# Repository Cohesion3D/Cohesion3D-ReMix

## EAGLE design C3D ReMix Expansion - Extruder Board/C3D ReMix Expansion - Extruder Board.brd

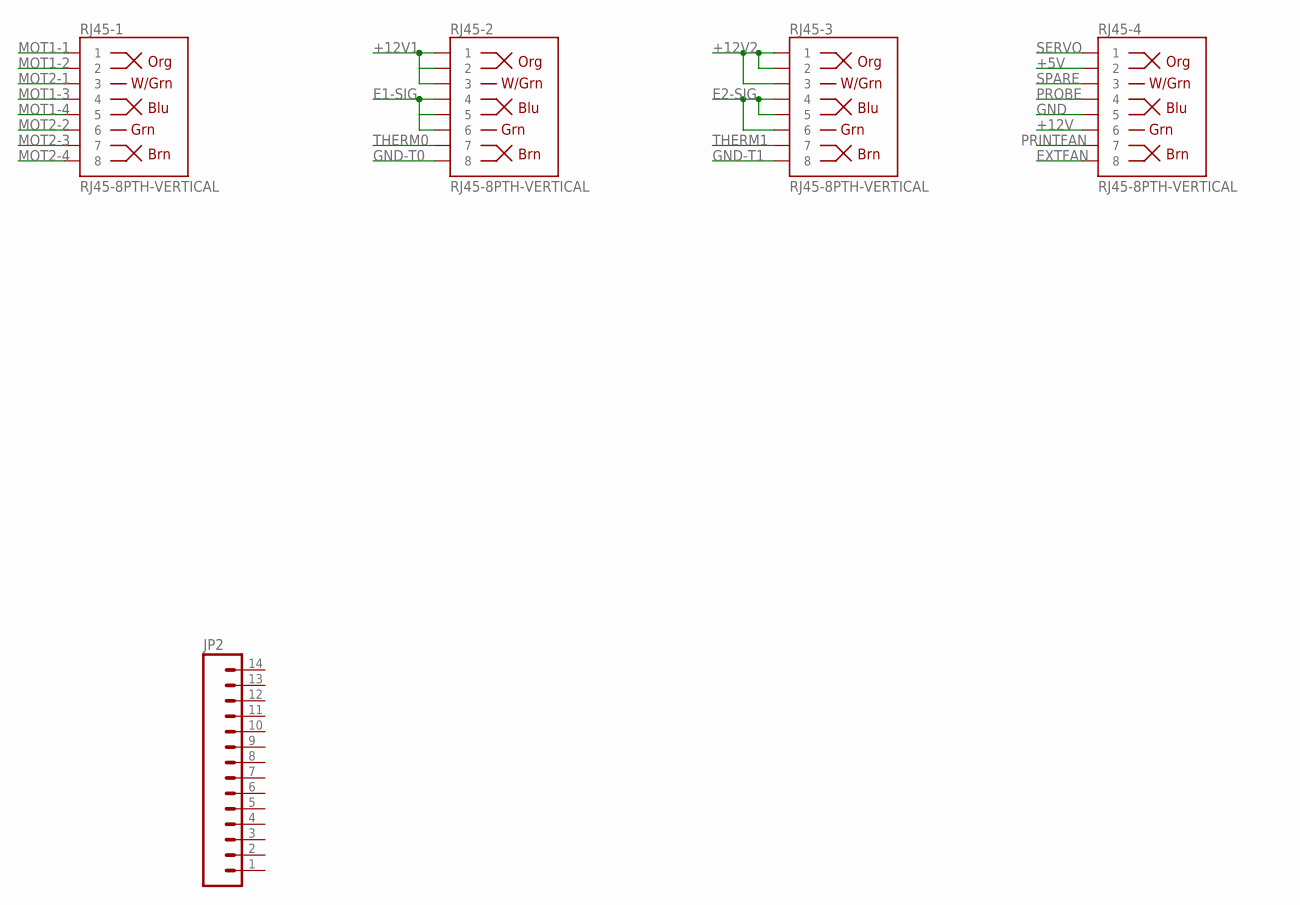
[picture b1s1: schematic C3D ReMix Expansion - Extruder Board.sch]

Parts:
JP2: M14; 1X14
RJ45-1, RJ45-2, RJ45-3, RJ45-4: RJ45-8PTH-VERTICAL; RJ45-8

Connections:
+5V: RJ45-4.2
+12V: RJ45-4.6
+12V1: RJ45-2.1, RJ45-2.2, RJ45-2.3
+12V2: RJ45-3.1, RJ45-3.2, RJ45-3.3
E1-SIG: RJ45-2.4, RJ45-2.5, RJ45-2.6
E2-SIG: RJ45-3.4, RJ45-3.5, RJ45-3.6
EXTFAN: RJ45-4.8
GND: RJ45-4.5
GND-T0: RJ45-2.8
GND-T1: RJ45-3.8
MOT1-1: RJ45-1.1
MOT1-2: RJ45-1.2
MOT1-3: RJ45-1.4
MOT1-4: RJ45-1.5
MOT2-1: RJ45-1.3
MOT2-2: RJ45-1.6
MOT2-3: RJ45-1.7
MOT2-4: RJ45-1.8
PRINTFAN: RJ45-4.7
PROBE: RJ45-4.4
SERVO: RJ45-4.1
SPARE: RJ45-4.3
THERM0: RJ45-2.7
THERM1: RJ45-3.7

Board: 2 copper layers, 5 parts (0 on the bottom side), 4 nets, no tracks yet.

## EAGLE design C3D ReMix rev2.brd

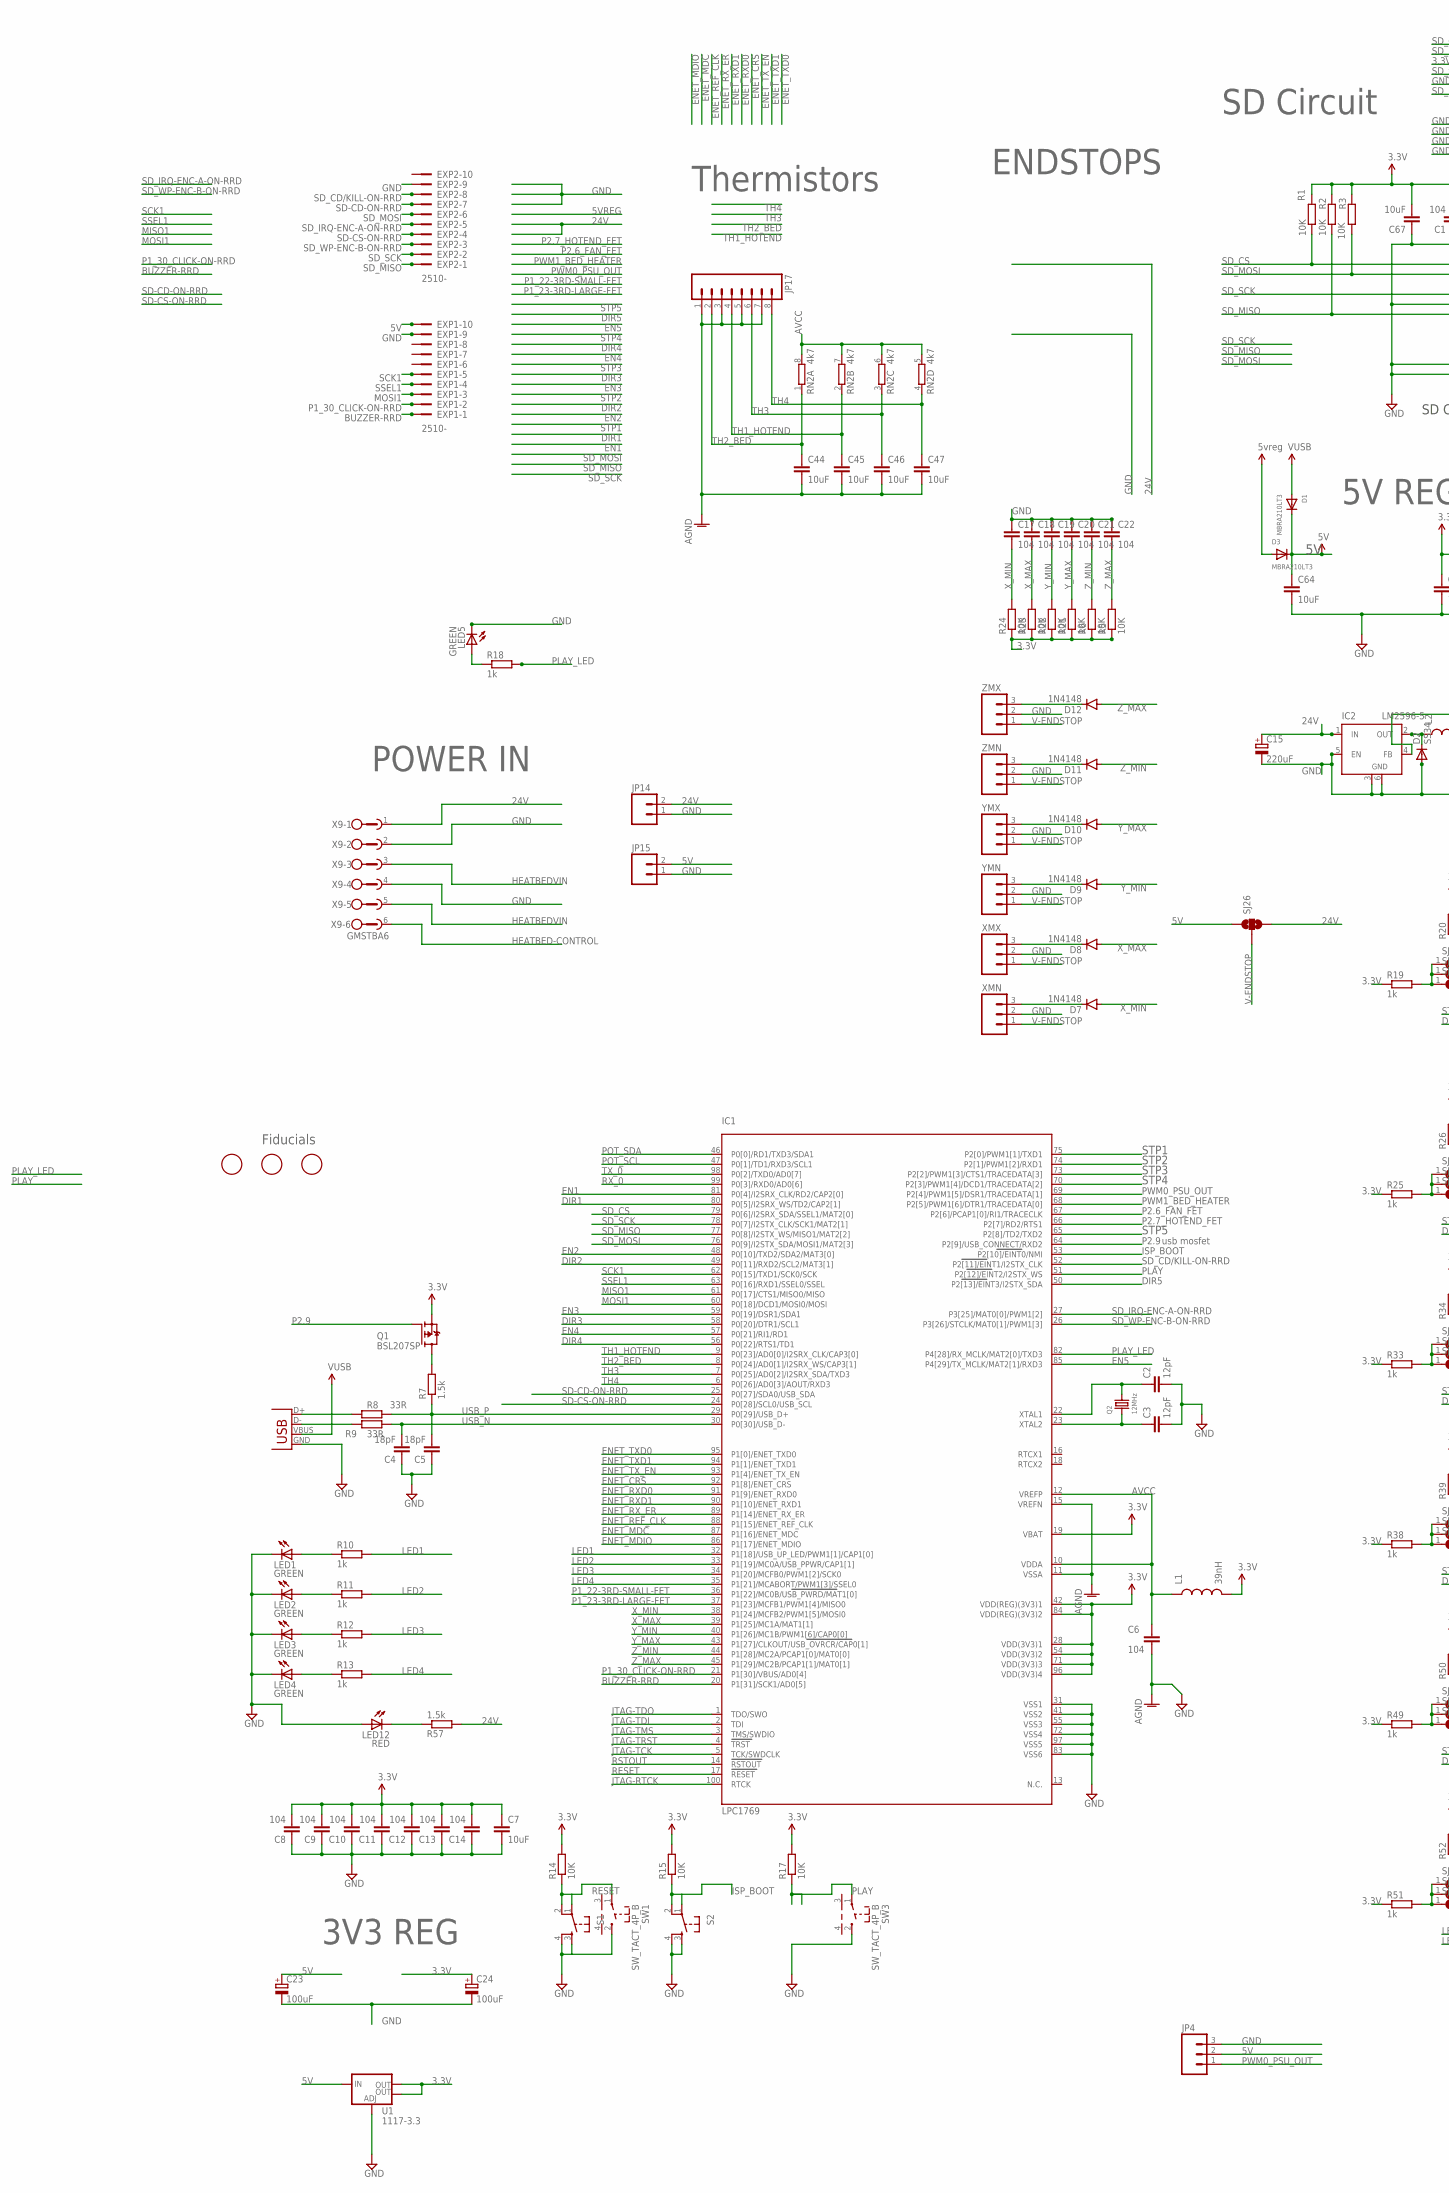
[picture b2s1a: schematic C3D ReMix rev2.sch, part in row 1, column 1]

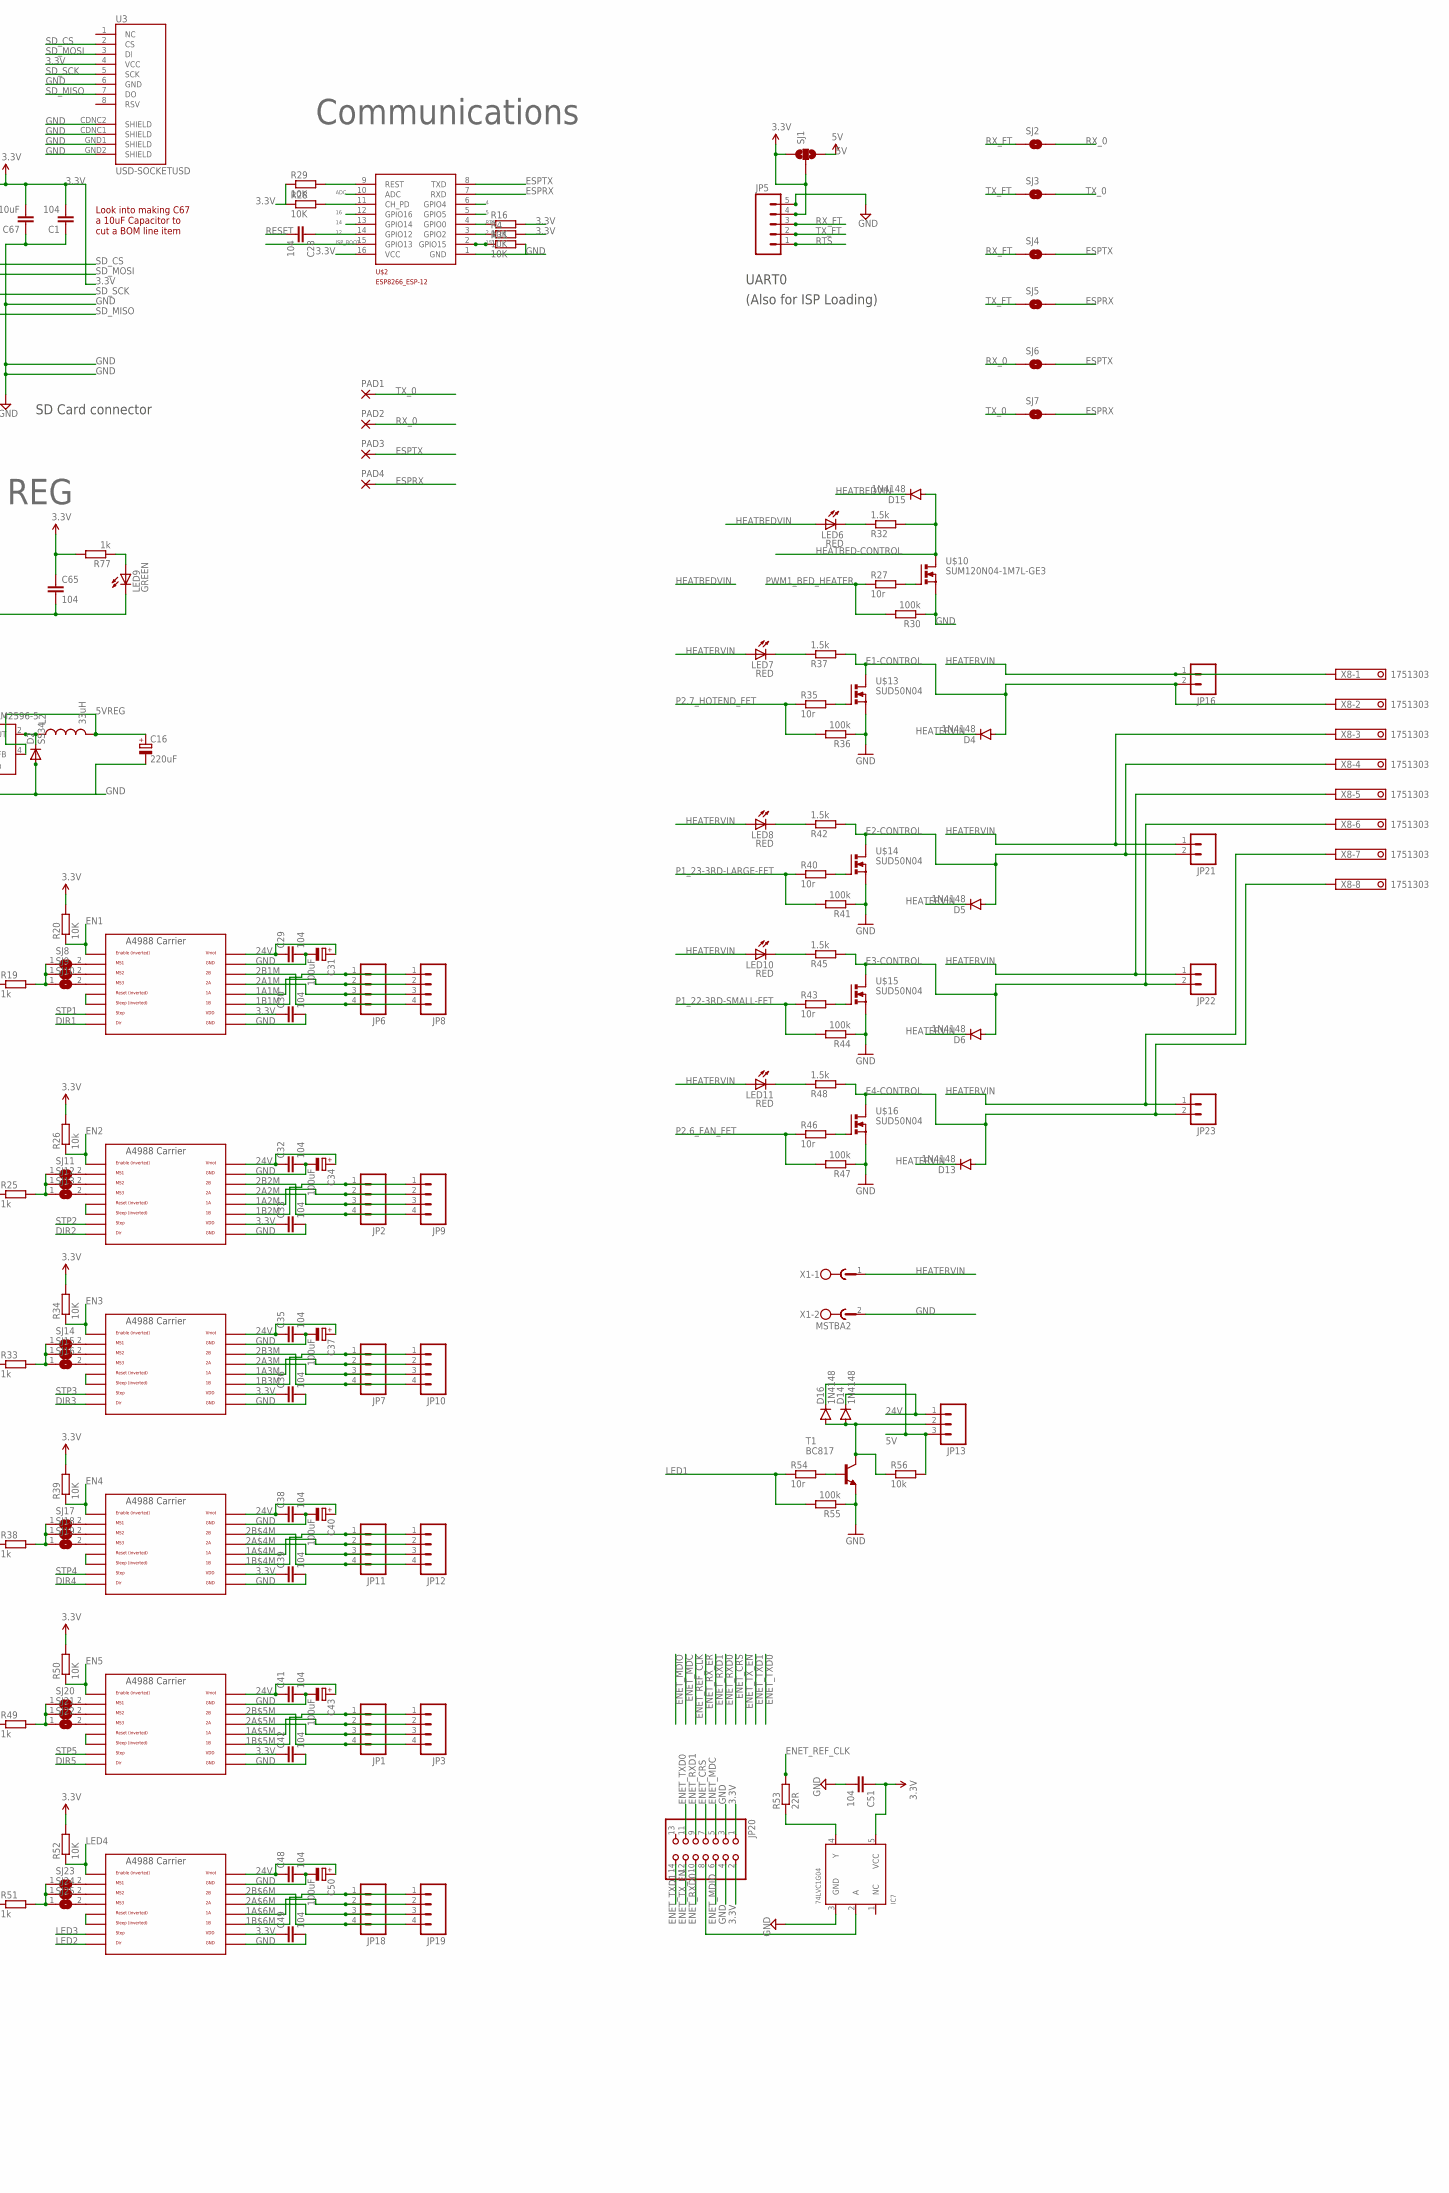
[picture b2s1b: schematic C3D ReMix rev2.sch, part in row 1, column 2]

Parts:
C1, C6, C8, C9, C10, C11, C12, C13, C14, C17, C18, C19, C20, C21, C22, C28, C29, C30, C32, C33, C35, C36, C38, C39, C41, C42, C48, C49, C51, C65: 104; C0603
C2, C3: 12pF; C0603
C4, C5: 18pF; C0603
C7, C44, C45, C46, C47, C64, C67: 10uF; C0603
C15, C16: 220uF; 153CLV-0810
C23, C24, C31, C34, C37, C40, C43, C50: 100uF; 153CLV-0605
D1, D3: MBRA210LT3; SMADIODE
D2: SS34; DO-214AC
D4, D5, D6, D7, D8, D9, D10, D11, D12, D13, D14, D15, D16: 1N4148; SOD-323
EXP1, EXP2: 2510-; PAK100/2500-10
IC1: LPC1769; LQFP100
IC2: LM2596-5; TO263-5
IC7: 74LVC1G04; SOT23-5
JP1, JP2, JP6, JP7, JP11, JP18: M04POLAR_LOCK; MOLEX-1X4_LOCK
JP3, JP8, JP9, JP10, JP12, JP19: M04LOCK; 1X04_LOCK
JP4, JP13: M03LOCK; 1X03_LOCK
JP5: M05NO_SILK; 1X05_NO_SILK
JP14, JP15, JP16, JP21, JP22, JP23: M02LOCK; 1X02_LOCK
JP17: M08LOCK; 1X08_LOCK
JP20: PINHD-2X7; 2X07
L1: 39nH; 0603
L2: 33uH; CDRH125
LED1, LED2, LED3, LED4, LED5, LED9: GREEN; SML0603
LED6, LED7, LED8, LED10, LED11, LED12: RED; SML0603
PAD1, PAD2, PAD3, PAD4: 1,6/0,9
Q1: BSL207SP; SC74_INFINEON
Q2: 12MHz; CRYSTAL_3.2X2.5
R1, R2, R3, R4, R5, R6, R14, R15, R16, R17, R20, R21, R22, R23, R24, R28, R29, R31, R34, R39, R50, R52: 10K; R0603
R7, R32, R37, R42, R45, R48, R57: 1.5k; R0603
R8, R9: 33R; R0603
R10, R11, R12, R13, R18, R19, R25, R33, R38, R49, R51, R77: 1k; R0603
R26, R56: 10k; R0603
R27, R35, R40, R43, R46, R54: 10r; R0603
R30, R36, R41, R44, R47, R55: 100k; R0603
R53: 22R; R0603
RN2: 4k7; 0603-ARV
S1, S2: TAC_SWITCHSMD; TACTILE_SWITCH_SMD
SJ1, SJ26: SOLDERJUMPER_2WAYS; SJ_3
SJ2, SJ3, SJ4, SJ5, SJ6, SJ7: SOLDERJUMPERNC; SJ_2S
SJ8, SJ9, SJ10, SJ11, SJ12, SJ13, SJ14, SJ15, SJ16, SJ17, SJ18, SJ19, SJ20, SJ21, SJ22, SJ23, SJ24, SJ25: SJ
SW1, SW3: SW_TACT_4P_B; SW_TACT_STANDARD_RIGHT_ANGLE
T1: BC817; SOT23-BEC
U1: 1117-3.3; SOT223
U3: USD-SOCKETUSD; USD-SOCKET-PP
U$1, U$5, U$6, U$7, U$8, U$9: POLOLU_A4983CARRIER; A4988BREAKOUT
U$2: ESP8266_ESP-12; ESP8266-ESP12
U$10: SUM120N04-1M7L-GE3; D2PACK
U$11, U$12, U$17: FIDUCIAL; FIDUCIAL_1MM
U$13, U$14, U$15, U$16: SUD50N04; D-PAK_TO252AA
X1: MSTBA2
X8: 1751303
X9: GMSTBA6
X14: USBPTH; USB-B-PTH
XMN: M03POLAR_LOCK; MOLEX-1X3_LOCK
XMX: M03POLAR_LOCK; MOLEX-1X3_LOCK
YMN: M03POLAR_LOCK; MOLEX-1X3_LOCK
YMX: M03POLAR_LOCK; MOLEX-1X3_LOCK
ZMN: M03POLAR_LOCK; MOLEX-1X3_LOCK
ZMX: M03POLAR_LOCK; MOLEX-1X3_LOCK

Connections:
1A1M: JP6.2, JP8.2, U$1.1A
1A2M: JP2.2, JP9.2, U$5.1A
1A3M: JP7.2, JP10.2, U$6.1A
1A$4M: JP11.2, JP12.2, U$7.1A
1A$5M: JP1.2, JP3.2, U$8.1A
1A$6M: JP18.2, JP19.2, U$9.1A
1B1M: JP6.1, JP8.1, U$1.1B
1B2M: JP2.1, JP9.1, U$5.1B
1B3M: JP7.1, JP10.1, U$6.1B
1B$4M: JP11.1, JP12.1, U$7.1B
1B$5M: JP1.1, JP3.1, U$8.1B
1B$6M: JP18.1, JP19.1, U$9.1B
2: R4.1, U$2.3 (GPIO2)
2A1M: JP6.3, JP8.3, U$1.2A
2A2M: JP2.3, JP9.3, U$5.2A
2A3M: JP7.3, JP10.3, U$6.2A
2A$4M: JP11.3, JP12.3, U$7.2A
2A$5M: JP1.3, JP3.3, U$8.2A
2A$6M: JP18.3, JP19.3, U$9.2A
2B1M: JP6.4, JP8.4, U$1.2B
2B2M: JP2.4, JP9.4, U$5.2B
2B3M: JP7.4, JP10.4, U$6.2B
2B$4M: JP11.4, JP12.4, U$7.2B
2B$5M: JP1.4, JP3.4, U$8.2B
2B$6M: JP18.4, JP19.4, U$9.2B
3.3V: C1.2, C7.1, C8.2, C9.2, C10.2, C11.2, C12.2, C13.2, C14.2, C24.+, C30.1, C33.1, C36.1, C39.1, C42.1, C49.1, C51.1, C65.1, C67.2, IC1.19 (VBAT), IC1.28 (VDD(3V3)1), IC1.42 (VDD(REG)(3V3)1), IC1.54 (VDD(3V3)2), IC1.71 (VDD(3V3)3), IC1.84 (VDD(REG)(3V3)2), IC1.96 (VDD(3V3)4), IC7.5 (VCC), JP5.4, JP20.1, JP20.2, L1.2, Q1.4 (S), R1.2, R2.2, R3.2, R4.2, R5.1, R6.1, R14.2, R15.2, R16.2, R17.2, R19.1, R20.2, R21.1, R22.1, R23.1, R24.1, R25.1, R26.2, R28.1, R29.1, R33.1, R34.2, R38.1, R39.2, R49.1, R50.2, R51.1, R52.2, R77.2, SJ1.1, SJ1.2, U1.2 (OUT), U1.4 (OUT), U3.4 (VCC), U$1.VDD, U$2.16 (VCC), U$5.VDD, U$6.VDD, U$7.VDD, U$8.VDD, U$9.VDD
4: U$2.6 (GPIO4)
5: U$2.5 (GPIO5)
5V: C23.+, C64.1, D1.C, D3.C, D16.C, EXP1.10, JP4.2, JP13.3, JP15.2, R56.2, SJ1.3, SJ26.1, U1.3 (IN)
5VREG: C16.+, D3.A, IC2.4 (FB), L2.2
12: C28.1, U$2.14 (GPIO12)
14: U$2.13 (GPIO14)
15: R31.1, U$2.2 (GPIO15)
16: U$2.12 (GPIO16)
24V: C15.+, C29.1, C31.+, C32.1, C34.+, C35.1, C37.+, C38.1, C40.+, C41.1, C43.+, C48.1, C50.+, D14.C, IC2.1 (IN), JP13.1, JP14.2, R57.2, SJ26.3, U$1.VMOT, U$5.VMOT, U$6.VMOT, U$7.VMOT, U$8.VMOT, U$9.VMOT, X9.1
ADC: U$2.10 (ADC)
AGND: C6.2, C44.2, C45.2, C46.2, C47.2, IC1.11 (VSSA), IC1.15 (VREFN), JP17.1, JP17.3, JP17.5, JP17.7
AVCC: C6.1, IC1.10 (VDDA), IC1.12 (VREFP), L1.1, RN2.5 (2), RN2.6 (2), RN2.7 (2), RN2.8 (2)
BUZZER-RRD: EXP1.1, IC1.20 (P1[31]/SCK1/AD0[5])
DIR1: IC1.80 (P0[5]/I2SRX_WS/TD2/CAP2[1]), U$1.DIR
DIR2: IC1.49 (P0[11]/RXD2/SCL2/MAT3[1]), U$5.DIR
DIR3: IC1.58 (P0[20]/DTR1/SCL1), U$6.DIR
DIR4: IC1.56 (P0[22]/RTS1/TD1), U$7.DIR
DIR5: IC1.50 (P2[13]/EINT3/I2STX_SDA), U$8.DIR
E1-CONTROL: D4.A, JP16.2, R37.2, U$13.4 (D), X8.2
E2-CONTROL: D5.A, JP21.2, R42.2, U$14.4 (D), X8.4
E3-CONTROL: D6.A, JP22.2, R45.2, U$15.4 (D), X8.6
E4-CONTROL: D13.A, JP23.2, R48.2, U$16.4 (D), X8.8
EN1: IC1.81 (P0[4]/I2SRX_CLK/RD2/CAP2[0]), R20.1, U$1.EN
EN2: IC1.48 (P0[10]/TXD2/SDA2/MAT3[0]), R26.1, U$5.EN
EN3: IC1.59 (P0[19]/DSR1/SDA1), R34.1, U$6.EN
EN4: IC1.57 (P0[21]/RI1/RD1), R39.1, U$7.EN
EN5: IC1.85 (P4[29]/TX_MCLK/MAT2[1]/RXD3), R50.1, U$8.EN
ENET_CRS: IC1.92 (P1[8]/ENET_CRS), JP20.7
ENET_MDC: IC1.87 (P1[16]/ENET_MDC), JP20.5
ENET_MDIO: IC1.86 (P1[17]/ENET_MDIO), JP20.6
ENET_REF_CLK: IC1.88 (P1[15]/ENET_REF_CLK), R53.2
ENET_RXD0: IC1.91 (P1[9]/ENET_RXD0), JP20.10
ENET_RXD1: IC1.90 (P1[10]/ENET_RXD1), JP20.9
ENET_RX_ER: IC1.89 (P1[14]/ENET_RX_ER)
ENET_TXD0: IC1.95 (P1[0]/ENET_TXD0), JP20.11
ENET_TXD1: IC1.94 (P1[1]/ENET_TXD1), JP20.14
ENET_TX_EN: IC1.93 (P1[4]/ENET_TX_EN), JP20.12
ESPRX: PAD4.1, SJ5.2, SJ7.2, U$2.7 (RXD)
ESPTX: PAD3.1, SJ4.2, SJ6.2, U$2.8 (TXD)
GND: C1.1, C2.2, C3.2, C4.1, C5.1, C7.2, C8.1, C9.1, C10.1, C11.1, C12.1, C13.1, C14.1, C15.-, C16.-, C17.1, C18.1, C19.1, C20.1, C21.1, C22.1, C23.-, C24.-, C29.2, C30.2, C31.-, C32.2, C33.2, C34.-, C35.2, C36.2, C37.-, C38.2, C39.2, C40.-, C41.2, C42.2, C43.-, C48.2, C49.2, C50.-, C51.2, C64.2, C65.2, C67.1, D2.2 (A), EXP1.9, EXP2.9, IC1.31 (VSS1), IC1.41 (VSS2), IC1.55 (VSS3), IC1.72 (VSS4), IC1.83 (VSS6), IC1.97 (VSS5), IC2.3 (GND), IC2.5 (EN), IC2.6 (GND), IC7.3 (GND), JP4.3, JP5.5, JP14.1, JP15.1, JP20.3, JP20.4, LED1.C, LED2.C, LED3.C, LED4.C, LED5.C, LED9.C, LED12.A, R30.1, R31.2, R36.1, R41.1, R44.1, R47.1, R55.1, S1.3, S1.4, S2.3, S2.4, SW1.2, SW3.2, T1.E, U1.1 (ADJ), U3.6 (GND), U3.CDNC1 (SHIELD), U3.CDNC2 (SHIELD), U3.GND1 (SHIELD), U3.GND2 (SHIELD), U$1.GND, U$1.GND@0 (GND), U$2.1 (GND), U$5.GND, U$5.GND@0 (GND), U$6.GND, U$6.GND@0 (GND), U$7.GND, U$7.GND@0 (GND), U$8.GND, U$8.GND@0 (GND), U$9.GND, U$9.GND@0 (GND), U$10.3 (S), U$13.3 (S), U$14.3 (S), U$15.3 (S), U$16.3 (S), X1.2, X9.2, X9.4, X14.GND, XMN.2, XMX.2, YMN.2, YMX.2, ZMN.2, ZMX.2
HEATBED-CONTROL: D15.A, R32.2, U$10.2 (D), X9.6
HEATBEDVIN: D15.C, LED6.A, X9.3, X9.5
HEATERVIN: D4.C, D5.C, D6.C, D13.C, JP16.1, JP21.1, JP22.1, JP23.1, LED7.A, LED8.A, LED10.A, LED11.A, X1.1, X8.1, X8.3, X8.5, X8.7
ISP_BOOT: IC1.53 (P2[10]/EINT0/NMI), R15.1, S2.1, S2.2, U$2.15 (GPIO13)
JTAG-RTCK: IC1.100 (RTCK)
JTAG-TCK: IC1.5 (TCK/SWDCLK)
JTAG-TDI: IC1.2 (TDI)
JTAG-TDO: IC1.1 (TDO/SWO)
JTAG-TMS: IC1.3 (TMS/SWDIO)
JTAG-TRST: IC1.4 (TRST)
LED1: IC1.32 (P1[18]/USB_UP_LED/PWM1[1]/CAP1[0]), R10.2, R54.1, R55.2
LED2: IC1.33 (P1[19]/MC0A/USB_PPWR/CAP1[1]), R11.2, U$9.DIR
LED3: IC1.34 (P1[20]/MCFB0/PWM1[2]/SCK0), R12.2, U$9.STEP
LED4: IC1.35 (P1[21]/MCABORT/PWM1[3]/SSEL0), R13.2, R52.1, U$9.EN
MISO1: IC1.61 (P0[17]/CTS1/MISO0/MISO)
MOSI1: EXP1.3, IC1.60 (P0[18]/DCD1/MOSI0/MOSI)
unnamed: C2.1, IC1.22 (XTAL1), Q2.2
unnamed: C3.1, IC1.23 (XTAL2), Q2.1
unnamed: LED5.A, R18.1
unnamed: D11.C, ZMN.3
unnamed: D10.C, YMX.3
unnamed: SJ8.2, U$1.MS1
unnamed: D9.C, YMN.3
unnamed: SJ9.2, U$1.MS2
unnamed: D2.1 (C), IC2.2 (OUT), L2.1
unnamed: SJ10.2, U$1.MS3
unnamed: D8.C, XMX.3
unnamed: U$5.RST, U$5.SLP (SLEEP)
unnamed: D7.C, XMN.3
unnamed: R25.2, SJ11.1, SJ12.1, SJ13.1
unnamed: SJ11.2, U$5.MS1
unnamed: D12.C, ZMX.3
unnamed: SJ12.2, U$5.MS2
unnamed: R28.2, U$2.11 (CH_PD)
unnamed: SJ13.2, U$5.MS3
unnamed: R27.2, U$10.1 (G)
unnamed: LED6.C, R32.1
unnamed: U$6.RST, U$6.SLP (SLEEP)
unnamed: LED12.C, R57.1
unnamed: R33.2, SJ14.1, SJ15.1, SJ16.1
unnamed: SJ14.2, U$6.MS1
unnamed: SJ15.2, U$6.MS2
unnamed: SJ16.2, U$6.MS3
unnamed: R35.2, U$13.1 (G)
unnamed: R19.2, SJ8.1, SJ9.1, SJ10.1
unnamed: LED7.C, R37.1
unnamed: U$7.RST, U$7.SLP (SLEEP)
unnamed: R38.2, SJ17.1, SJ18.1, SJ19.1
unnamed: SJ17.2, U$7.MS1
unnamed: SJ18.2, U$7.MS2
unnamed: U$1.RST, U$1.SLP (SLEEP)
unnamed: SJ19.2, U$7.MS3
unnamed: R40.2, U$14.1 (G)
unnamed: LED8.C, R42.1
unnamed: R43.2, U$15.1 (G)
unnamed: LED10.C, R45.1
unnamed: R46.2, U$16.1 (G)
unnamed: LED11.C, R48.1
unnamed: U$8.RST, U$8.SLP (SLEEP)
unnamed: R49.2, SJ20.1, SJ21.1, SJ22.1
unnamed: SJ20.2, U$8.MS1
unnamed: SJ21.2, U$8.MS2
unnamed: SJ22.2, U$8.MS3
unnamed: U$9.RST, U$9.SLP (SLEEP)
unnamed: R51.2, SJ23.1, SJ24.1, SJ25.1
unnamed: SJ23.2, U$9.MS1
unnamed: Q1.1 (D), Q1.2 (D), Q1.5 (D), Q1.6 (D), R7.2
unnamed: SJ24.2, U$9.MS2
unnamed: SJ25.2, U$9.MS3
unnamed: R54.2, T1.B
unnamed: D14.A, D16.A, JP13.2, R56.1, T1.C
unnamed: R8.1, X14.D+
unnamed: R9.1, X14.D-
unnamed: IC7.2 (A), JP20.8
unnamed: IC7.4 (Y), R53.1
unnamed: LED9.A, R77.1
unnamed: LED4.A, R13.1
unnamed: LED3.A, R12.1
unnamed: LED2.A, R11.1
unnamed: LED1.A, R10.1
P1_22-3RD-SMALL-FET: IC1.36 (P1[22]/MC0B/USB_PWRD/MAT1[0]), R43.1, R44.2
P1_23-3RD-LARGE-FET: IC1.37 (P1[23]/MCFB1/PWM1[4]/MISO0), R40.1, R41.2
P1_30_CLICK-ON-RRD: EXP1.2, IC1.21 (P1[30]/VBUS/AD0[4])
P2.6_FAN_FET: IC1.67 (P2[6]/PCAP1[0]/RI1/TRACECLK), R46.1, R47.2
P2.7_HOTEND_FET: IC1.66 (P2[7]/RD2/RTS1), R35.1, R36.2
P2.9: IC1.64 (P2[9]/USB_CONNECT/RXD2), Q1.3 (G)
PLAY: IC1.51 (P2[12]/EINT2/I2STX_WS), R17.1, SW3.1
PLAY_LED: IC1.82 (P4[28]/RX_MCLK/MAT2[0]/TXD3), R18.2
POT_SCL: IC1.47 (P0[1]/TD1/RXD3/SCL1)
POT_SDA: IC1.46 (P0[0]/RD1/TXD3/SDA1)
PWM0_PSU_OUT: IC1.69 (P2[4]/PWM1[5]/DSR1/TRACEDATA[1]), JP4.1
PWM1_BED_HEATER: IC1.68 (P2[5]/PWM1[6]/DTR1/TRACEDATA[0]), R27.1, R30.2
RESET: C28.2, IC1.17 (RESET), R14.1, S1.1, S1.2, SW1.1
RESET1: R29.2, U$2.9 (REST)
RSTOUT: IC1.14 (RSTOUT)
RTS: JP5.1, R16.1, U$2.4 (GPIO0)
RX_0: IC1.99 (P0[3]/RXD0/AD0[6]), PAD2.1, SJ2.2, SJ6.1
RX_FT: JP5.3, SJ2.1, SJ4.1
SCK1: EXP1.5, IC1.62 (P0[15]/TXD1/SCK0/SCK)
SD-CD-ON-RRD: EXP2.7, IC1.25 (P0[27]/SDA0/USB_SDA)
SD-CS-ON-RRD: EXP2.4, IC1.24 (P0[28]/SCL0/USB_SCL)
SD_CD/KILL-ON-RRD: EXP2.8, IC1.52 (P2[11]/EINT1/I2STX_CLK)
SD_CS: IC1.79 (P0[6]/I2SRX_SDA/SSEL1/MAT2[0]), R1.1, U3.2 (CS)
SD_IRQ-ENC-A-ON-RRD: EXP2.5, IC1.27 (P3[25]/MAT0[0]/PWM1[2])
SD_MISO: EXP2.1, IC1.77 (P0[8]/I2STX_WS/MISO1/MAT2[2]), R2.1, U3.7 (DO)
SD_MOSI: EXP2.6, IC1.76 (P0[9]/I2STX_SDA/MOSI1/MAT2[3]), R3.1, U3.3 (DI)
SD_SCK: EXP2.2, IC1.78 (P0[7]/I2STX_CLK/SCK1/MAT2[1]), U3.5 (SCK)
SD_WP-ENC-B-ON-RRD: EXP2.3, IC1.26 (P3[26]/STCLK/MAT0[1]/PWM1[3])
SSEL1: EXP1.4, IC1.63 (P0[16]/RXD1/SSEL0/SSEL)
STP1: IC1.75 (P2[0]/PWM1[1]/TXD1), U$1.STEP
STP2: IC1.74 (P2[1]/PWM1[2]/RXD1), U$5.STEP
STP3: IC1.73 (P2[2]/PWM1[3]/CTS1/TRACEDATA[3]), U$6.STEP
STP4: IC1.70 (P2[3]/PWM1[4]/DCD1/TRACEDATA[2]), U$7.STEP
STP5: IC1.65 (P2[8]/TD2/TXD2), U$8.STEP
TH1_HOTEND: C45.1, IC1.9 (P0[23]/AD0[0]/I2SRX_CLK/CAP3[0]), JP17.4, RN2.2 (1)
TH2_BED: C44.1, IC1.8 (P0[24]/AD0[1]/I2SRX_WS/CAP3[1]), JP17.2, RN2.1
TH3: C46.1, IC1.7 (P0[25]/AD0[2]/I2SRX_SDA/TXD3), JP17.6, RN2.3 (1)
TH4: C47.1, IC1.6 (P0[26]/AD0[3]/AOUT/RXD3), JP17.8, RN2.4 (1)
TX_0: IC1.98 (P0[2]/TXD0/AD0[7]), PAD1.1, SJ3.2, SJ7.1
TX_FT: JP5.2, SJ3.1, SJ5.1
USB_N: C4.2, IC1.30 (P0[30]/USB_D-), R9.2
USB_P: C5.2, IC1.29 (P0[29]/USB_D+), R7.1, R8.2
V-ENDSTOP: SJ26.2, XMN.1, XMX.1, YMN.1, YMX.1, ZMN.1, ZMX.1
VUSB: D1.A, X14.VBUS
X_MAX: C18.2, D8.A, IC1.39 (P1[25]/MC1A/MAT1[1]), R23.2
X_MIN: C17.2, D7.A, IC1.38 (P1[24]/MCFB2/PWM1[5]/MOSI0), R24.2
Y_MAX: C20.2, D10.A, IC1.43 (P1[27]/CLKOUT/USB_OVRCR/CAP0[1]), R21.2
Y_MIN: C19.2, D9.A, IC1.40 (P1[26]/MC1B/PWM1[6]/CAP0[0]), R22.2
Z_MAX: C22.2, D12.A, IC1.45 (P1[29]/MC2B/PCAP1[1]/MAT0[1]), R5.2
Z_MIN: C21.2, D11.A, IC1.44 (P1[28]/MC2A/PCAP1[0]/MAT0[0]), R6.2

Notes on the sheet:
SD Card connector
UART0
(Also for ISP Loading)
usb mosfet
5V REG
SD Circuit
Communications
3V3 REG
ENDSTOPS
Look into making C67 a 10uF Capacitor to cut a BOM line item
Thermistors
Fiducials
POWER IN

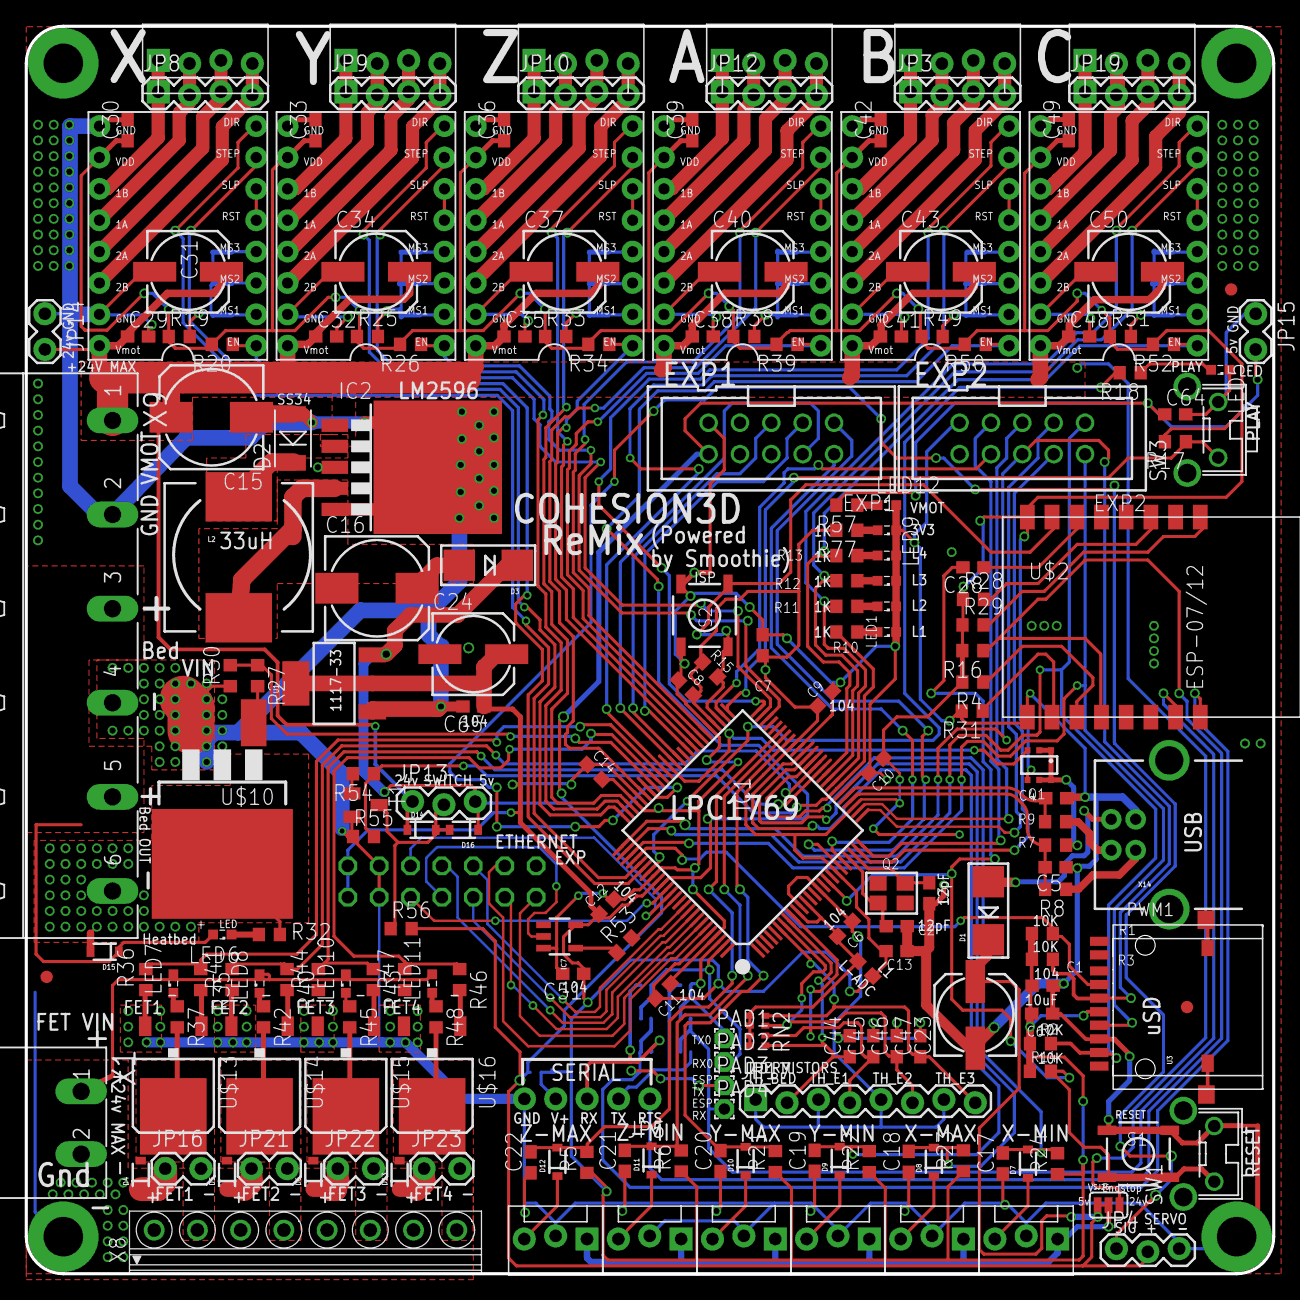
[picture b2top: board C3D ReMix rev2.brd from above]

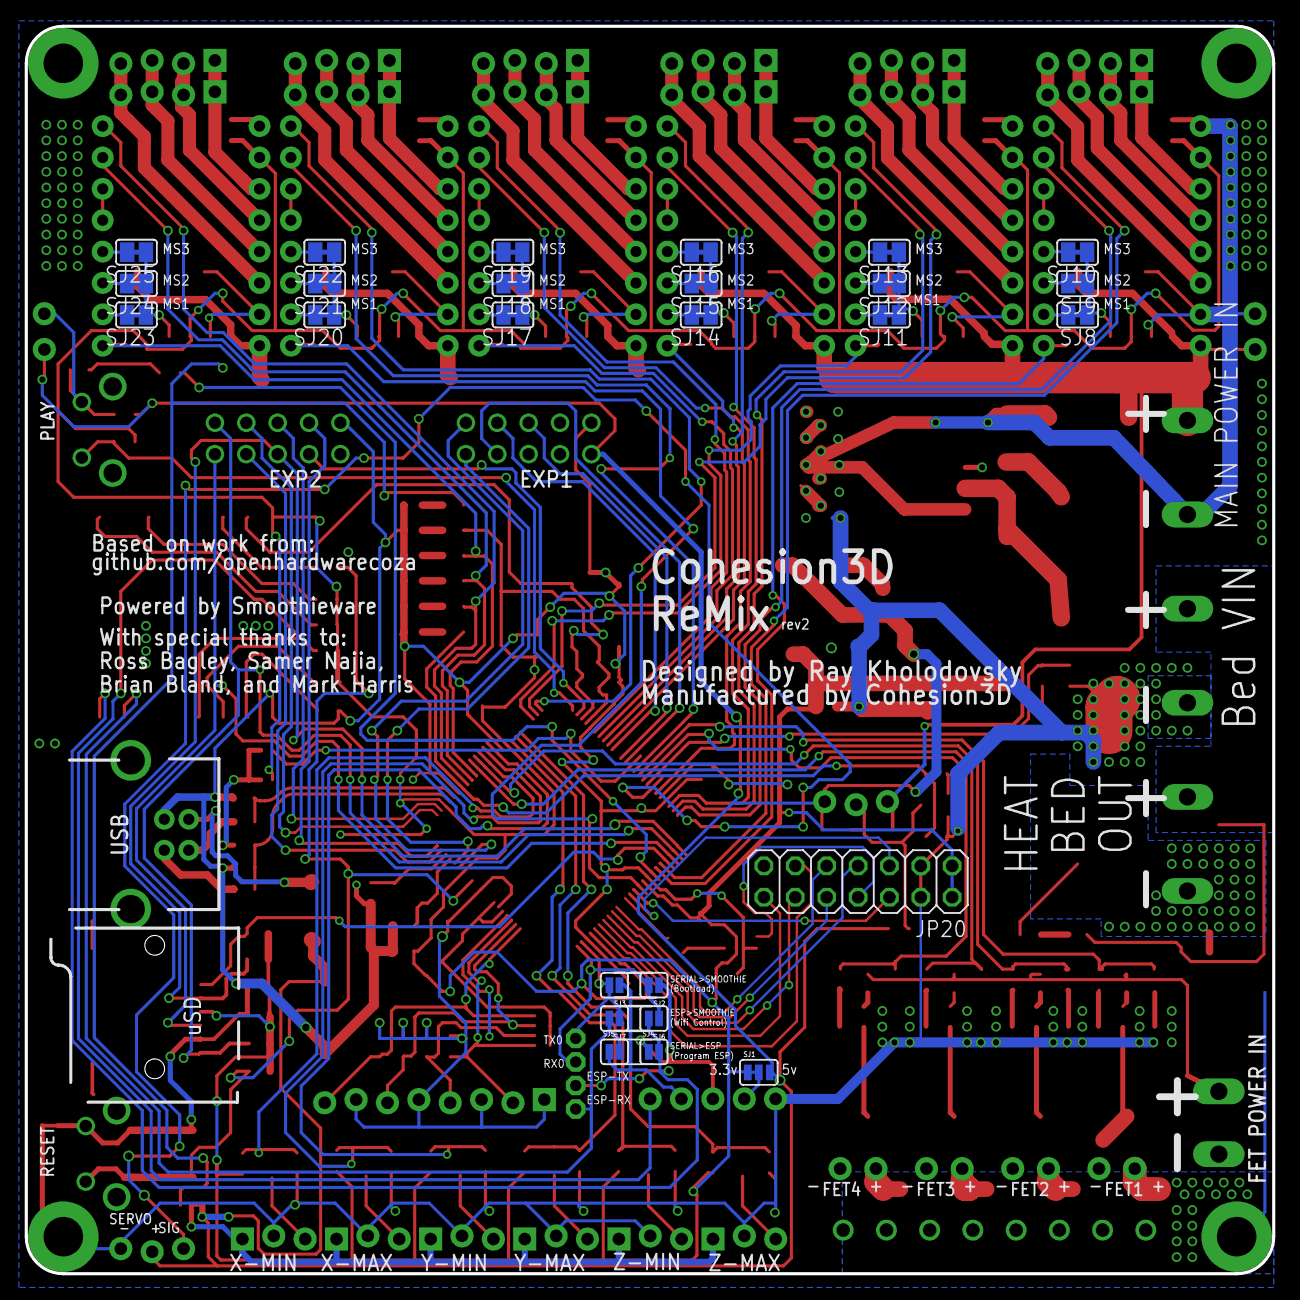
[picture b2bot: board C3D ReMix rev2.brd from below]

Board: 2 copper layers, 101.0 x 101.0 mm, 232 parts (26 on the bottom side), 180 nets.

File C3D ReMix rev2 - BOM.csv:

"Qty";"Value";"Device";"Package";"Parts";"Description";"MF";"MPN";"OC_FARNELL";"OC_NEWARK";"PROD_ID";"VALUE";
"4";"";"1,6/0,9";"1,6/0,9";"PAD1, PAD2, PAD3, PAD4";"THROUGH-HOLE PAD";"";"";"";"";"";"";
"6";"";"M02LOCK";"1X02_LOCK";"JP14, JP15, JP16, JP21, JP22, JP23";"Standard 2-pin 0.1" header. Use with";"";"";"";"";"";"";
"2";"";"M03LOCK";"1X03_LOCK";"JP4, JP13";"Header 3";"";"";"";"";"";"";
"6";"";"M03POLAR_LOCK";"MOLEX-1X3_LOCK";"XMN, XMX, YMN, YMX, ZMN, ZMX";"Header 3";"";"";"";"";"";"";
"6";"";"M04LOCK";"1X04_LOCK";"JP3, JP8, JP9, JP10, JP12, JP19";"Header 4";"";"";"";"";"";"";
"6";"";"M04POLAR_LOCK";"MOLEX-1X4_LOCK";"JP1, JP2, JP6, JP7, JP11, JP18";"Header 4";"";"";"";"";"";"";
"1";"";"M05NO_SILK";"1X05_NO_SILK";"JP5";"Header 5";"";"";"";"";"";"";
"1";"";"M08LOCK";"1X08_LOCK";"JP17";"Header 8";"";"";"";"";"";"";
"1";"";"PINHD-2X7";"2X07";"JP20";"PIN HEADER";"";"";"";"";"";"";
"18";"";"SJ";"SJ";"SJ8, SJ9, SJ10, SJ11, SJ12, SJ13, SJ14, SJ15, SJ16, SJ17, SJ18, SJ19, SJ20, SJ21, SJ22, SJ23, SJ24, SJ25";"SMD solder JUMPER";"";"";"";"";"";"";
"6";"";"SOLDERJUMPERNC";"SJ_2S";"SJ2, SJ3, SJ4, SJ5, SJ6, SJ7";"Solder Jumper";"";"";"";"";"";"";
"2";"";"SOLDERJUMPER_2WAYS";"SJ_3";"SJ1, SJ26";"Solder Jumper";"";"";"";"";"";"";
"2";"";"TAC_SWITCHSMD";"TACTILE_SWITCH_SMD";"S1, S2";"Momentary Switch";"";"";"";"";"";"";
"2";"1.5K";"R-EU_R0603";"R0603";"R7, R57";"RESISTOR, European symbol";"";"";"";"";"";"";
"5";"1.5k";"R-EU_R0603";"R0603";"R32, R37, R42, R45, R48";"RESISTOR, European symbol";"";"";"";"";"";"";
"6";"100k";"R-EU_R0603";"R0603";"R30, R36, R41, R44, R47, R55";"RESISTOR, European symbol";"";"";"";"";"";"";
"2";"100u";"CPOL-EU153CLV-0605";"153CLV-0605";"C23, C24";"POLARIZED CAPACITOR, European symbol";"";"";"";"";"";"";
"6";"100uF";"CPOL-EU153CLV-0605";"153CLV-0605";"C31, C34, C37, C40, C43, C50";"POLARIZED CAPACITOR, European symbol";"";"";"";"";"";"";
"30";"104";"C-EUC0603";"C0603";"C1, C17, C18, C19, C20, C21, C22, C28, C29, C30, C32, C33, C35, C36, C38, C39, C41, C42, C48, C49, C51, C65, C6, C8, C9, C10, C11, C12, C13, C14";"CAPACITOR, European symbol";"";"";"";"";"";"";
"11";"10K";"R-EU_R0603";"R0603";"R1, R2, R3, R4, R14, R15, R16, R17, R28, R29, R31";"RESISTOR, European symbol";"";"";"";"";"";"";
"12";"10k";"R-EU_R0603";"R0603";"R5, R6, R20, R21, R22, R23, R24, R26, R34, R39, R50, R52";"RESISTOR, European symbol";"";"";"";"";"";"";
"6";"10r";"R-EU_R0603";"R0603";"R27, R35, R40, R43, R46, R54";"RESISTOR, European symbol";"";"";"";"";"";"";
"7";"10uF";"C-EUC0603";"C0603";"C7, C44, C45, C46, C47, C64, C67";"CAPACITOR, European symbol";"";"";"";"";"";"";
"1";"1117-3.3";"V_REG_LM1117SOT223";"SOT223";"U1";"Voltage Regulator LM1117";"";"";"";"";"VREG-08170";"";
"1";"12MHz";"CRYSTALTHIN";"CRYSTAL_3.2X2.5";"Q2";"Crystals";"";"";"";"";"";"";
"2";"12pF";"C-EUC0603";"C0603@1";"C2, C3";"CAPACITOR, European symbol";"";"";"";"";"";"";
"4";"1751248";"1751248";"1751248";"X4, X5, X6, X7";"MKDS 1/ 2-3,5 Printklemme";"";"";"unknown";"unknown";"";"";
"2";"18pF";"C-EUC0603";"C0603@1";"C4, C5";"CAPACITOR, European symbol";"";"";"";"";"";"";
"13";"1N4148";"DIODEBAS16";"SOD-323";"D4, D5, D6, D7, D8, D9, D10, D11, D12, D13, D14, D15, D16";"Diode";"";"";"";"";"DIO-09646";"250mA/100V";
"12";"1k";"R-EU_R0603";"R0603";"R10, R11, R12, R13, R18, R19, R25, R33, R38, R49, R51, R77";"RESISTOR, European symbol";"";"";"";"";"";"";
"2";"220u";"CPOL-EUE2.5-7";"E2,5-7";"C26, C27";"POLARIZED CAPACITOR, European symbol";"";"";"";"";"";"";
"1";"22R";"R-EU_R0603";"R0603";"R53";"RESISTOR, European symbol";"";"";"";"";"";"";
"2";"2510-";"2510-";"PAK100/2500-10";"EXP1, EXP2";"3M (TM) Pak 100 4-Wall Header";"3M";"2510-6002UB";"9838244";"46F4725";"";"";
"2";"33R";"R-EU_R0603";"R0603";"R8, R9";"RESISTOR, European symbol";"";"";"";"";"";"";
"1";"33uH";"INDUCTORPWR";"CDRH125";"L2";"Inductors";"";"";"";"";"";"";
"1";"39nH";"INDUCTOR0603";"0603";"L1";"Inductors";"";"";"";"";"";"";
"1";"4k7";"4R-N0603-ARV";"0603-ARV";"RN2";"Array Chip Resistor";"";"";"unknown";"unknown";"";"";
"1";"74LVC1G04";"74LVC1G04";"SOT23-5";"IC7";"74LVC1G04 - Single Inverter Gate";"";"";"";"";"";"";
"1";"BC817";"BC817-40-NPN-SOT23-BEC";"SOT23-BEC";"T1";"NPN Transistror";"";"";"";"";"";"";
"1";"BSL207SP";"BSL207SP";"SC74_INFINEON";"Q1";"OptiMOS(R)-P Small-Signal-Transistor P-Channel, Enhancement mode, Super Logic Level (2.5 V rated)";"";"";"";"";"";"";
"1";"ESP8266_ESP-12";"ESP8266_ESP-12";"ESP8266-ESP12";"U$2";"ESP8266 ESP-12";"";"";"";"";"";"";
"6";"FIDUCIAL";"FIDUCIAL";"FIDUCIAL_1MM";"U$11, U$12, U$17, U$18, U$19, U$20";"For use by pick and place machines to calibrate the vision/machine, 1mm";"";"";"";"";"";"";
"1";"GMSTBA2";"GMSTBA2";"GMSTBA2";"X2";"PHOENIX";"FARNELL";"1757242";"3705171";"71C4161";"";"";
"1";"GMSTBA4";"GMSTBA4";"GMSTBA4";"X3";"PHOENIX";"FARNELL";"1757268";"3705195";"71C4163";"";"";
"6";"GREEN";"LEDSML0603";"SML0603";"LED1, LED2, LED3, LED4, LED5, LED9";"LED";"";"";"";"";"";"";
"4";"IRLR024";"N-POWER-MOSFETDPAK-MOSFET";"D-PAK_TO252AA";"U$13, U$14, U$15, U$16";"";"";"";"";"";"";"";
"1";"LM2596-5";"LM2596S";"TO263-5";"IC2";"STEP-DOWN VOLTAGE REGULATOR";"";"";"";"";"";"";
"1";"LPC1769";"LPC1768";"LQFP100";"IC1";"LPC1768 100 MHz 32-bit ARM Cortex-M3 based microcontroller featuring a high level of integration and low power consumption. 512 kB Flash, 64 kB SRAM, USB Device/Host/OTG, Ethernet, CAN, I2S, 10-bit DAC";"";"";"";"";"";"";
"2";"MBRA210LT3";"DIODESMA";"SMADIODE";"D1, D3";"Diode";"";"";"";"";"";"";
"1";"MSTBA2";"MSTBA2";"MSTBA2";"X1";"PHOENIX";"FARNELL";"1757242";"3705171";"71C4161";"";"";
"6";"POLOLU_A4983CARRIER";"POLOLU_A4983CARRIER";"A4988BREAKOUT";"U$1, U$5, U$6, U$7, U$8, U$9";"";"";"";"";"";"";"";
"6";"RED";"LEDSML0603";"SML0603";"LED6, LED7, LED8, LED10, LED11, LED12";"LED";"";"";"";"";"";"";
"1";"SS34";"DIODE-DO-214AC";"DO-214AC";"D2";"Various Diode Packages";"";"";"";"";"";"";
"1";"SUM120N04-1M7L-GE3";"N-POWER-MOSFETD2PAK-MOSFET";"D2PACK";"U$10";"";"";"";"";"";"";"";
"2";"SW_TACT_4P_B";"SW_TACT_4P_B";"SW_TACT_STANDARD_RIGHT_ANGLE";"SW1, SW3";"";"";"";"";"";"";"";
"1";"USBPTH";"USBPTH";"USB-B-PTH";"X14";"USB Connectors";"";"";"";"";"";"";
"1";"USD-SOCKETUSD";"USD-SOCKETUSD";"USD-SOCKET-PP";"U3";"microSD Socket";"";"";"";"";"";"";

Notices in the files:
parts and their libraries:
SparkFun-Connectors: Licensing: Creative Commons ShareAlike 4.0 International - https://creativecommons.org/licenses/by-sa/4.0
SparkFun-Passives: Licensing: CC v3.0 Share-Alike You are welcome to use this library for commercial purposes.
